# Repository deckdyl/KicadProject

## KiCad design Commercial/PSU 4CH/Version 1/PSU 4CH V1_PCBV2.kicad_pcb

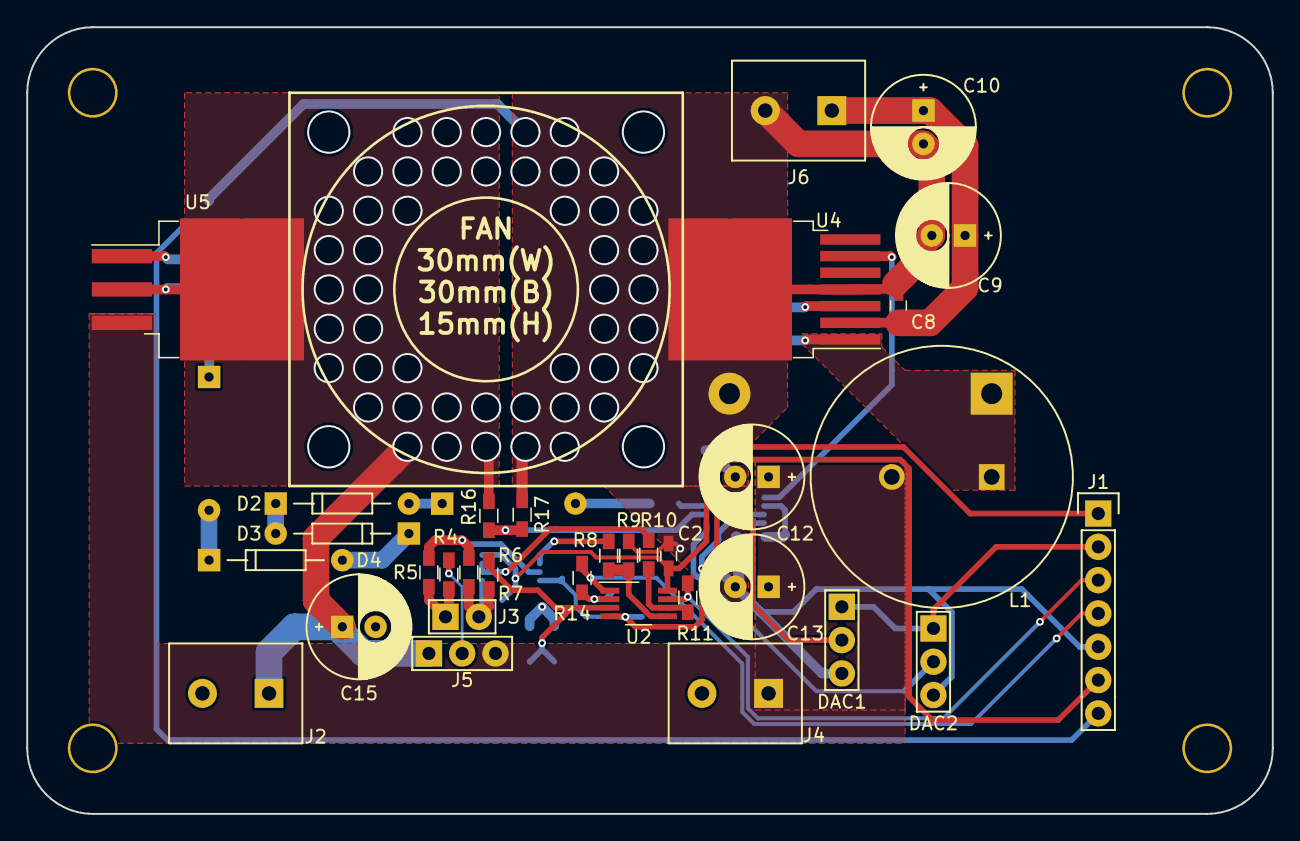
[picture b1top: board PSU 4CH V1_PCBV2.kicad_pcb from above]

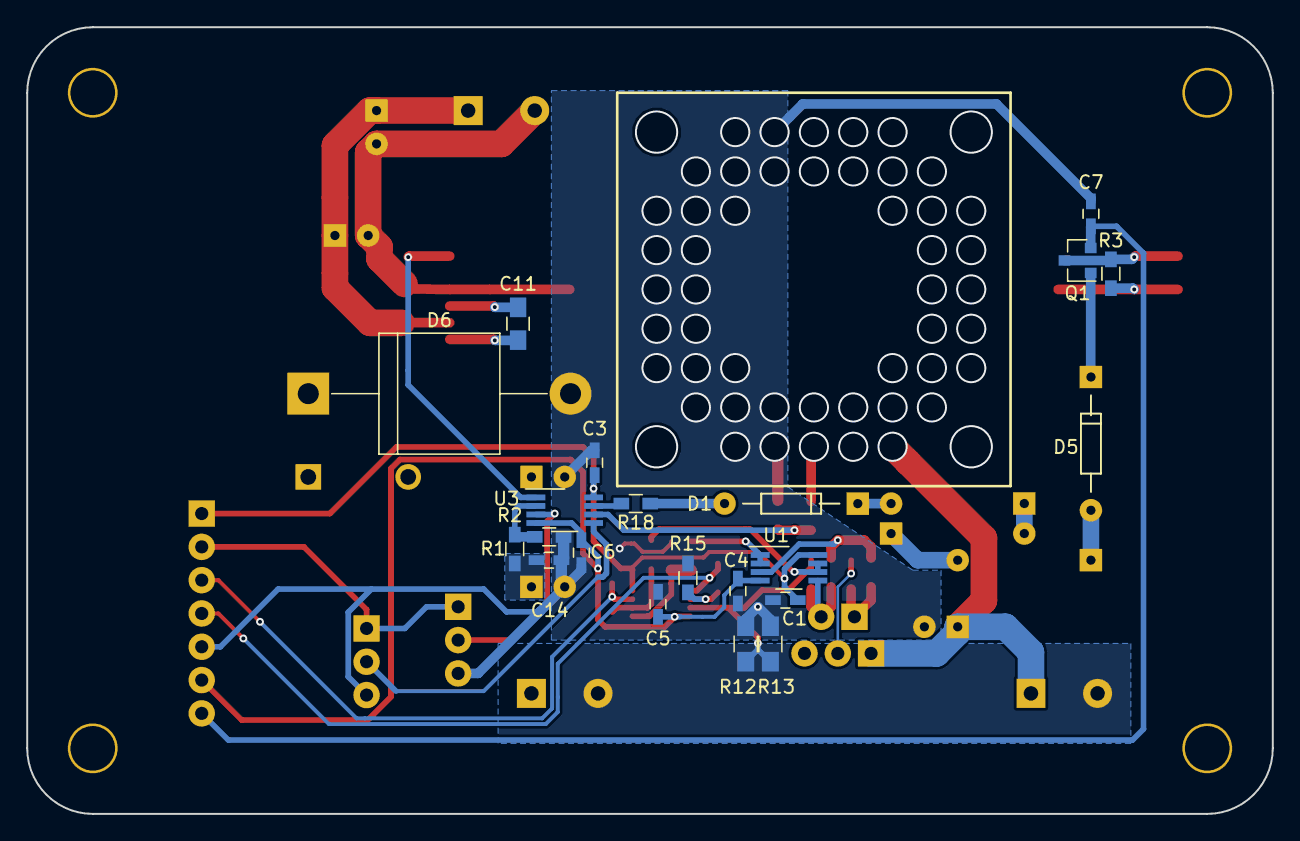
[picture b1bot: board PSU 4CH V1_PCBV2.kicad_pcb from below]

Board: 2 copper layers, 95.0 x 60.0 mm, 54 parts (21 on the bottom side), 35 nets.

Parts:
C1, C2, C3, C4, C5, C6, C7, C8, C14: 470nF; C_0603_HandSoldering
C9, C10, C12, C13, C15: 22uF; Cap_Pol_Radial_D8_P2
C11: 10nF; C_0805_HandSoldering
D1, D2, D3, D4, D5: 1N914; 1N4148
D6: 15SQ045; D_P600_R-6_P20.00mm_Horizontal
DAC1: BUCK_DAC; Pin_Header_Straight_1x03
DAC2: LINEAR DAC; Pin_Header_Straight_1x03
J1: MCU I/O; Pin_Header_Straight_1x07
J2, J4: PSU Out; Terminal_Block-5mm
J3: PSU FB; Pin_Header_Straight_1x02
J5: Select; Pin_Header_Straight_1x03
J6: Input; Terminal_Block-5mm
L1: 22uH; Inductor-22uH-5.4A
Q1: FJV1845; SOT-23
R1, R5, R16: 91kΩ; R_0603_HandSoldering
R2, R6, R17: 10kΩ; R_0603_HandSoldering
R3: 680Ω; R_0603_HandSoldering
R4, R7: 10Ω; R_0603_HandSoldering
R8, R9, R10, R11, R15: 1kΩ; R_0603_HandSoldering
R12, R13: 12mΩ; R_0805_HandSoldering
R14: 100kΩ; R_0603_HandSoldering
R18: 75kΩ; R_0603_HandSoldering
U1, U2, U3: LMP2022; VSSOP-8_3.0x3.0mm_Pitch0.65mm
U4: LM2678SX-ADJ; TO-263-7_TabPin4
U5: LMS1585A; TO-263-3_TabPin2

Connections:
+3V3: DAC1.1, DAC2.1, J1.2
+5V: C1.1, C2.1, C3.1, J1.1, U1.8, U2.8, U3.8
-0V5: C4.2, C5.2, C6.2, J1.6, U1.4, U2.4, U3.4
-2V8: C7.2, J1.7, Q1.2
/DAC_BUCK: DAC1.2, U3.3
/DAC_LINEAR: DAC2.2, U3.5
/I-ADC: J1.4, R14.1, U2.1
/Input-V+: C8.1, C9.1, C10.1, J6.1, U4.2
/Output-Buck: C12.1, C13.1, C14.1, J4.1, J5.3, L1.2, R1.1, U5.3
/Output-GND: J2.2, J4.2, R7.2, R12.1, R13.1, U2.3
/Output-Linear: C15.1, J2.1, J5.1, R3.1, R16.1, U5.2
/V-ADC: J1.3, R11.1, U2.7
/Vfb+: J3.1, R4.2, R5.1
/Vfb-: J3.2, R6.2, R7.1, U1.5
/Vfb-Buck: U3.1, U4.6
/Vfb-Linear: Q1.3, R3.2, U5.1
GND: C1.2, C2.2, C3.2, C4.1, C5.1, C6.1, C7.1, C8.2, C9.2, C10.2, C12.2, C13.2, C14.2, C15.2, D6.2, DAC1.3, DAC2.3, J1.5, J6.2, R2.2, R9.2, R12.2, R13.2, R15.2, R17.2, U4.4
unnamed: C11.1, D6.1, L1.1, U4.1
unnamed: C11.2, U4.3
unnamed: D1.1, D2.2
unnamed: D1.2, R18.1
unnamed: D2.1, D3.2
unnamed: D3.1, D4.2
unnamed: D4.1, D5.2
unnamed: D5.1, Q1.1
unnamed: J5.2, R4.1
unnamed: R1.2, R2.1, U3.2
unnamed: R5.2, R6.1, U1.3
unnamed: R8.1, R9.1, U2.5
unnamed: R8.2, U1.1, U1.2
unnamed: R10.1, R11.2, U2.6
unnamed: R10.2, U1.6, U1.7
unnamed: R14.2, R15.1, U2.2
unnamed: R16.2, R17.1, U3.6
unnamed: R18.2, U3.7

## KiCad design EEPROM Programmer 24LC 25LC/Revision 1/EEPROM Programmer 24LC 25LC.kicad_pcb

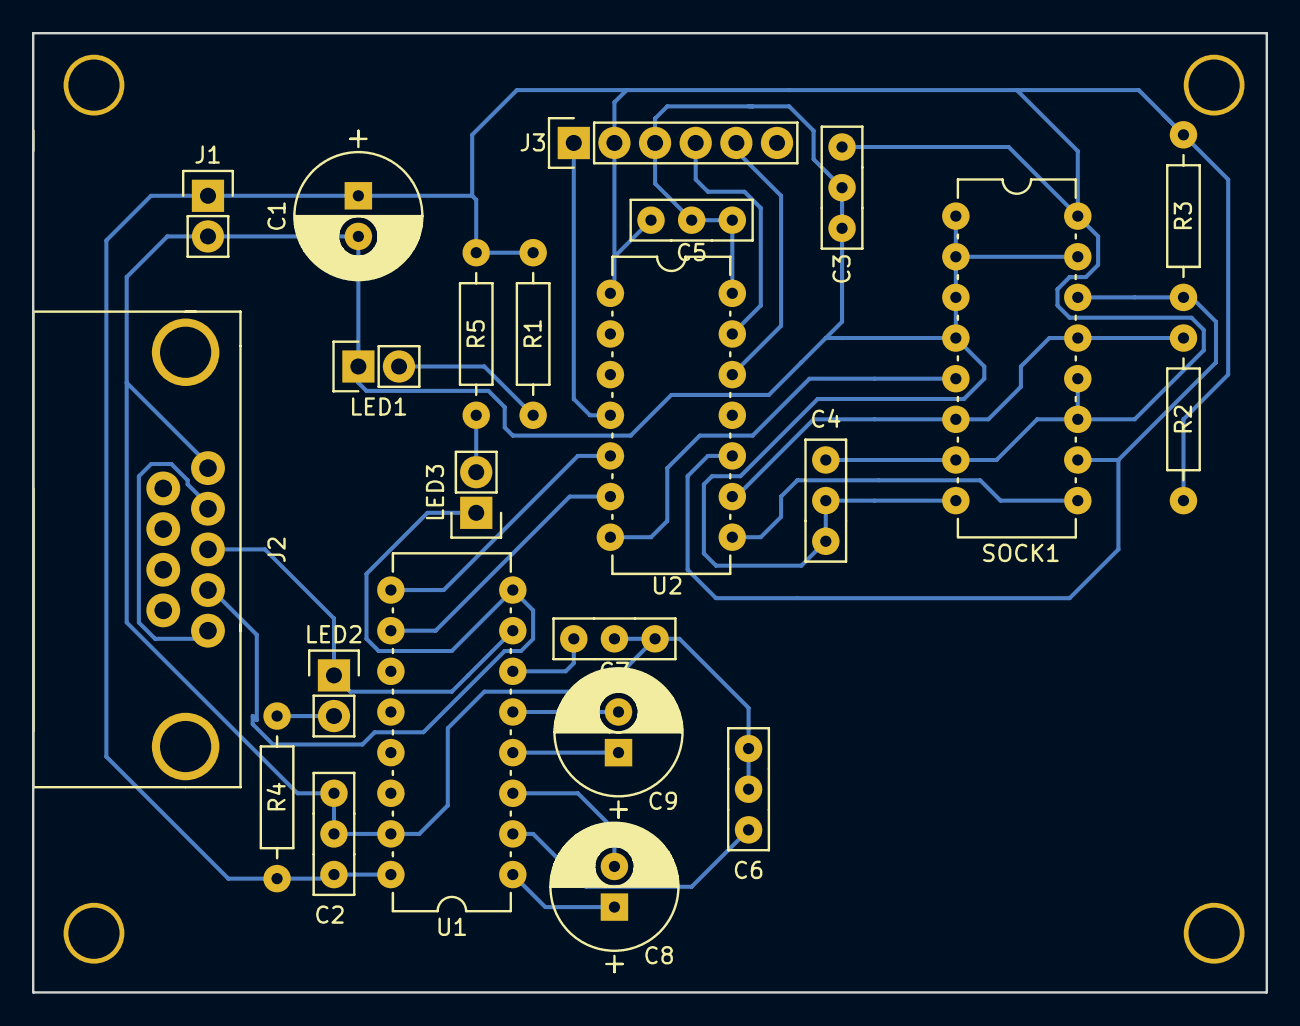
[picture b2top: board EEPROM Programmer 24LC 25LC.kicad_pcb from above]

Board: 2 copper layers, 77.1 x 59.9 mm, 23 parts (0 on the bottom side), 23 nets.

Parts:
C1: 100uF; Cap_Pol_Radial_D8_P2
C2, C3, C4, C5, C6, C7: 100nF; Cap_UnPol_P3
C8, C9: 1uF; Cap_Pol_Radial_D8_P2
J1: Power; Pin_Header_Straight_1x02
J2: RS232 DB9; RS232_DB9_Female_PCB_Mount
J3: PICKIT; Pin_Header_Straight_1x06
LED1: PWR_red; Pin_Header_Straight_1x02
LED2: RX_Yellow; Pin_Header_Straight_1x02
LED3: TX_Yellow; Pin_Header_Straight_1x02
R1: 390Ω; Resistor-0.25W
R2, R3: 4.7kΩ; Resistor-0.25W
R4, R5: 1kΩ; Resistor-0.25W
SOCK1: Test_Socket_16pin; IC_PDIP_16pin
U1: MAX232; IC_PDIP_16pin
U2: PIC16F1825; IC_PDIP_14pin

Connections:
+5V: C1.1, C2.1, C3.1, C4.1, C5.1, J1.1, J3.2, R1.2, R2.2, R3.2, R4.1, R5.1, SOCK1.7, SOCK1.11, SOCK1.12, SOCK1.16, U1.16, U2.1
CS: SOCK1.5, U2.7
GND: C1.2, C2.2, C3.2, C4.2, C5.2, C6.2, C7.2, J1.2, J2.5, J3.3, LED1.1, SOCK1.1, SOCK1.2, SOCK1.3, SOCK1.4, SOCK1.8, SOCK1.15, U1.15, U2.14
ICSPCLK: J3.5, U2.12
ICSPDAT: J3.4, U2.13
MCLR: J3.1, U2.4
M_SPI_In: R2.1, SOCK1.6, SOCK1.13, U2.9
M_SPI_Out: SOCK1.9, U2.8
unnamed: C6.1, U1.2
unnamed: C7.1, U1.6
unnamed: C8.1, U1.1
unnamed: C8.2, U1.3
unnamed: C9.1, U1.4
unnamed: C9.2, U1.5
unnamed: J2.1, J2.4
unnamed: J2.2, LED3.1, U1.8
unnamed: J2.3, LED2.1, U1.7
unnamed: LED1.2, R1.1
unnamed: LED2.2, R4.2
unnamed: LED3.2, R5.2
RX: U1.9, U2.5
SCK: R3.1, SOCK1.10, SOCK1.14, U2.10
TX: U1.10, U2.6

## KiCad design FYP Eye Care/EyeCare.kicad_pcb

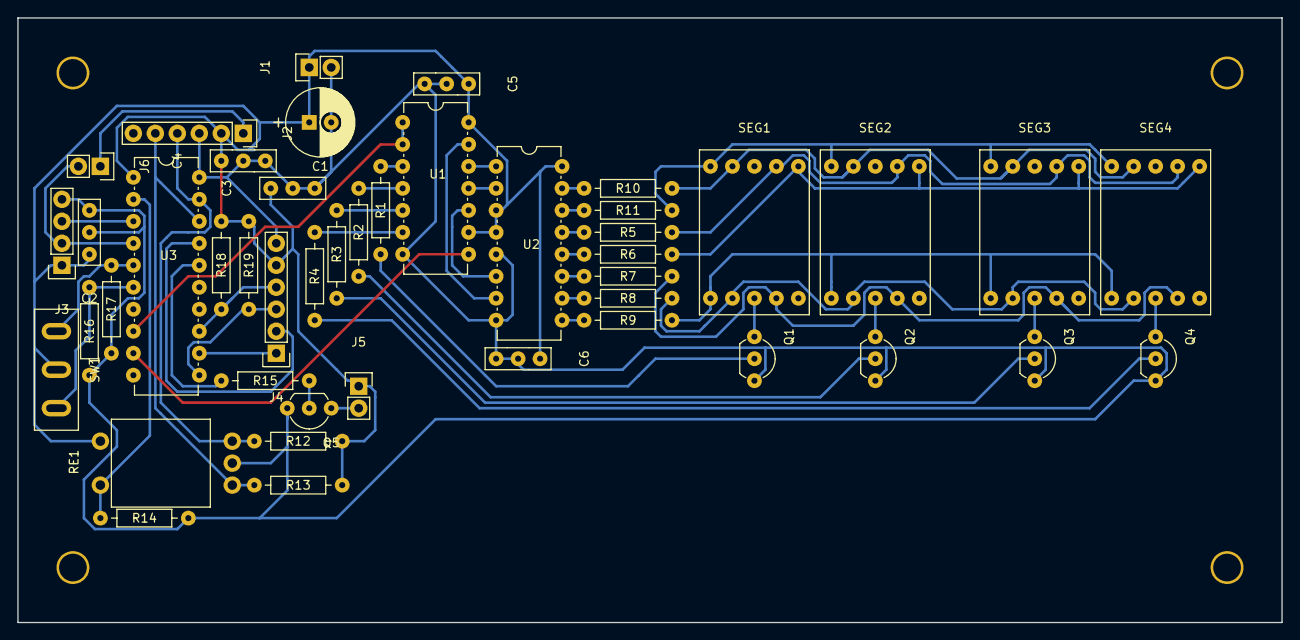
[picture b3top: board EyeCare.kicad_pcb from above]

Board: 2 copper layers, 146.1 x 69.9 mm, 45 parts (0 on the bottom side), 49 nets.

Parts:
C1: 100uF; Cap_Pol_Radial_D8_P2
C2, C3, C4, C5, C6: 100nF; Cap_UnPol_P3
J1: PWR; Pin_Header_Straight_1x02
J2: PICKIT; Pin_Header_Straight_1x06
J3: Sensor; Pin_Header_Straight_1x04
J4: DS3231; Pin_Header_Straight_1x06
J5: Buzzer; Pin_Header_Straight_1x02
J6: Jumper; Pin_Header_Straight_1x02
Q1, Q2, Q3, Q4, Q5: 2N3904; TO-92_Inline_Wide
R1, R2, R3, R4, R15: 470Ω; Resistor-0.25W
R5, R6, R7, R8, R9, R10, R11: 180Ω; Resistor-0.25W
R12, R13, R14, R16, R17: 10kΩ; Resistor-0.25W
R18, R19: 3.9kΩ; Resistor-0.25W
RE1: Rotary_Encoder
SEG1, SEG2, SEG3, SEG4: 7Segment_CC; 7Seg_small
SW1: Switch; Switch_3-Pin
U1: 74LS164; IC_PDIP_14pin
U2: 4511; IC_PDIP_16pin
U3: PIC16F1509; IC_PDIP_20pin

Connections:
32K: J4.1, U3.12
Buzzer: R15.1, U3.16
CLK: U1.8, U3.9
D0: Q4.2, R4.2
D1: Q3.2, R3.2
D2: Q2.2, R2.2
D3: Q1.2, R1.2
DI: U1.1, U1.2, U3.8
Echo: J3.3, U3.3
unnamed: J5.2, Q5.1
unnamed: Q1.1, SEG1.3,8
unnamed: Q2.1, SEG2.3,8
unnamed: Q3.1, SEG3.3,8
unnamed: Q4.1, SEG4.3,8
unnamed: Q5.2, R15.2
unnamed: R1.1, U1.3
unnamed: R2.1, U1.4
unnamed: R3.1, U1.5
unnamed: R4.1, U1.6
unnamed: R5.1, SEG1.7, SEG2.7, SEG3.7, SEG4.7
unnamed: R5.2, U2.13
unnamed: R6.1, SEG1.6, SEG2.6, SEG3.6, SEG4.6
unnamed: R6.2, U2.12
unnamed: R7.1, SEG1.4, SEG2.4, SEG3.4, SEG4.4
unnamed: R7.2, U2.11
unnamed: R8.1, SEG1.2, SEG2.2, SEG3.2, SEG4.2
unnamed: R8.2, U2.10
unnamed: R9.1, SEG1.1, SEG2.1, SEG3.1, SEG4.1
unnamed: R9.2, U2.9
unnamed: R10.1, SEG1.9, SEG2.9, SEG3.9, SEG4.9
unnamed: R10.2, U2.15
unnamed: R11.1, SEG1.10, SEG2.10, SEG3.10, SEG4.10
unnamed: R11.2, U2.14
unnamed: U1.10, U2.6
unnamed: U1.11, U2.2
unnamed: U1.12, U2.1
unnamed: U1.13, U2.7
PGC: J2.5, R13.2, RE1.5, U3.18
PGD: J2.4, R12.2, RE1.3, U3.19
RotarySW: R14.1, RE1.2, U3.2
SCL: J4.3, R19.2, U3.11
SDA: J4.4, R18.2, U3.13
SQW: J4.2, U3.17
SW1: R17.1, SW1.1, U3.5
SW2: R16.1, SW1.3, U3.6
Trigger: J3.2, J6.2, U3.4
Vdd: C1.1, C2.1, C3.1, C4.1, C5.1, C6.1, J1.1, J2.2, J3.1, J4.5, J5.1, R12.1, R13.1, R18.1, R19.1, RE1.1, SW1.2, U1.9, U1.14, U2.3, U2.4, U2.16, U3.1
Vpp: J2.1, J6.1
Vss: C1.2, C2.2, C3.2, C4.2, C5.2, C6.2, J1.2, J2.3, J3.4, J4.6, Q1.3, Q2.3, Q3.3, Q4.3, Q5.3, R14.2, R16.2, R17.2, RE1.4, U1.7, U2.5, U2.8, U3.20

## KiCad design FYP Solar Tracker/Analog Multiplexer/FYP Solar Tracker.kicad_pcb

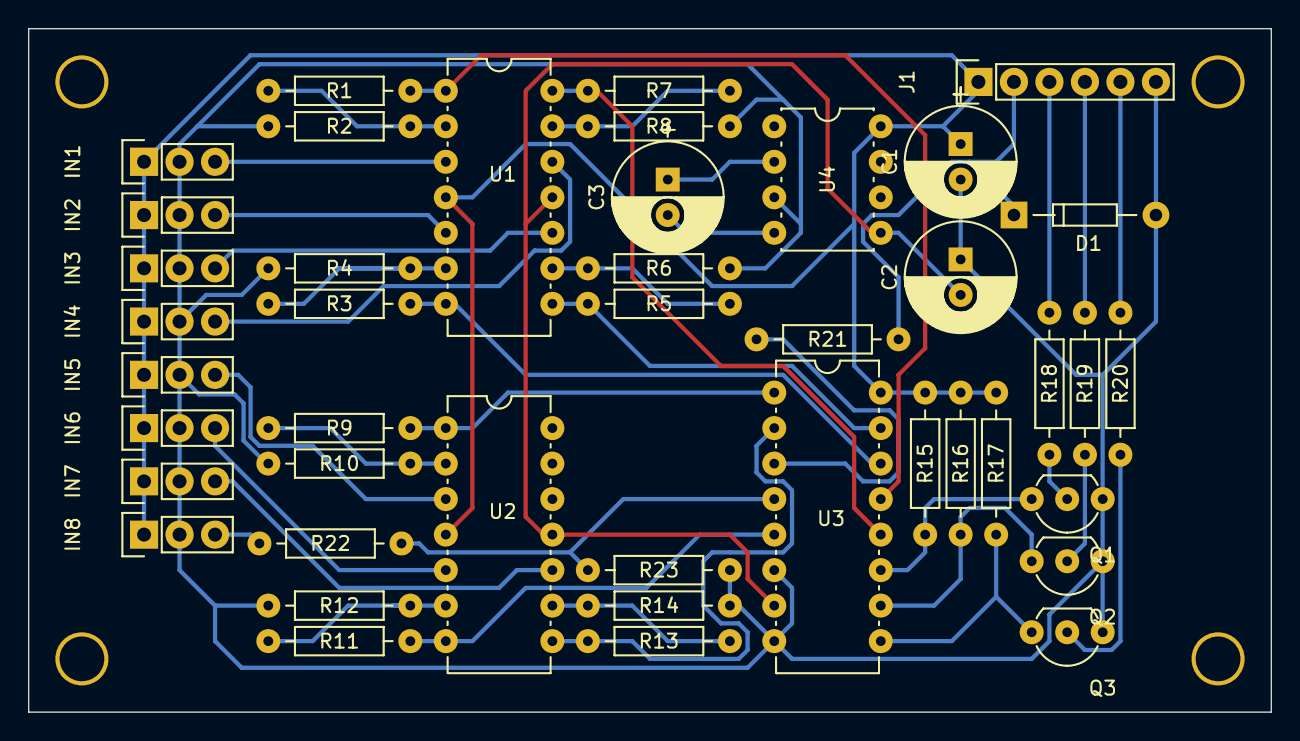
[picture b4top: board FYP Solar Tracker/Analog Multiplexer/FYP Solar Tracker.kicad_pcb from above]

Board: 2 copper layers, 88.9 x 48.9 mm, 43 parts (0 on the bottom side), 39 nets.

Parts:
C1, C2, C3: 10uF; Cap_Pol_Radial_D8_P2
D1: 4.7V; 1N4148
IN1, IN2, IN3, IN4, IN5, IN6, IN7, IN8: Header_1X3; Pin_Header_Straight_1x03
J1: MCU; Pin_Header_Straight_1x06
Q1, Q2, Q3: 2N3904; TO-92_Inline_Wide
R1, R3, R5, R9, R11, R13, R22: 27kΩ; Resistor-0.25W
R2, R4, R6, R7, R10, R12, R14, R15, R16, R17, R18, R19, R20, R23: 10kΩ; Resistor-0.25W
R8: 12kΩ; Resistor-0.25W
R21: 1.2kΩ; Resistor-0.25W
U1, U2: LM324; IC_PDIP_14pin
U3: 4051; IC_PDIP_16pin
U4: TC962; IC_PDIP_8pin

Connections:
+9V: C1.1, IN1.1, IN2.1, IN3.1, IN4.1, IN5.1, IN6.1, IN7.1, IN8.1, J1.1, R15.1, R16.1, R17.1, U1.4, U2.4, U3.16, U4.8
CH0: R1.1, U1.1, U3.13
CH1: R3.1, U1.7, U3.14
CH2: R5.1, U1.8, U3.15
CH3: R7.1, U1.14, U3.12
CH4: R9.1, U2.1, U3.1
CH5: R11.1, U2.7, U3.5
CH6: R13.1, U2.8, U3.2
CH7: R22.2, R23.1, U3.4
GND: C1.2, C2.1, D1.2, IN1.2, IN2.2, IN3.2, IN4.2, IN5.2, IN6.2, IN7.2, IN8.2, J1.6, Q1.1, Q2.1, Q3.1, R2.2, R4.2, R6.2, R8.2, R10.2, R12.2, R14.2, R23.2, U3.6, U3.8, U4.3
unnamed: C2.2, U1.11, U2.11, U3.7, U4.5
unnamed: C3.1, U4.2
unnamed: C3.2, U4.4
unnamed: D1.1, J1.2, R21.2
unnamed: IN1.3, U1.3
unnamed: IN2.3, U1.5
unnamed: IN3.3, U1.10
unnamed: IN4.3, U1.12
unnamed: IN5.3, U2.3
unnamed: IN6.3, U2.5
unnamed: IN7.3, U2.10
unnamed: IN8.3, R22.1
unnamed: J1.3, R18.1
unnamed: J1.4, R19.1
unnamed: J1.5, R20.1
unnamed: Q1.2, R18.2
unnamed: Q1.3, R15.2, U3.11
unnamed: Q2.2, R19.2
unnamed: Q2.3, R16.2, U3.10
unnamed: Q3.2, R20.2
unnamed: Q3.3, R17.2, U3.9
unnamed: R1.2, R2.1, U1.2
unnamed: R3.2, R4.1, U1.6
unnamed: R5.2, R6.1, U1.9
unnamed: R7.2, R8.1, U1.13
unnamed: R9.2, R10.1, U2.2
unnamed: R11.2, R12.1, U2.6
unnamed: R13.2, R14.1, U2.9
unnamed: R21.1, U3.3

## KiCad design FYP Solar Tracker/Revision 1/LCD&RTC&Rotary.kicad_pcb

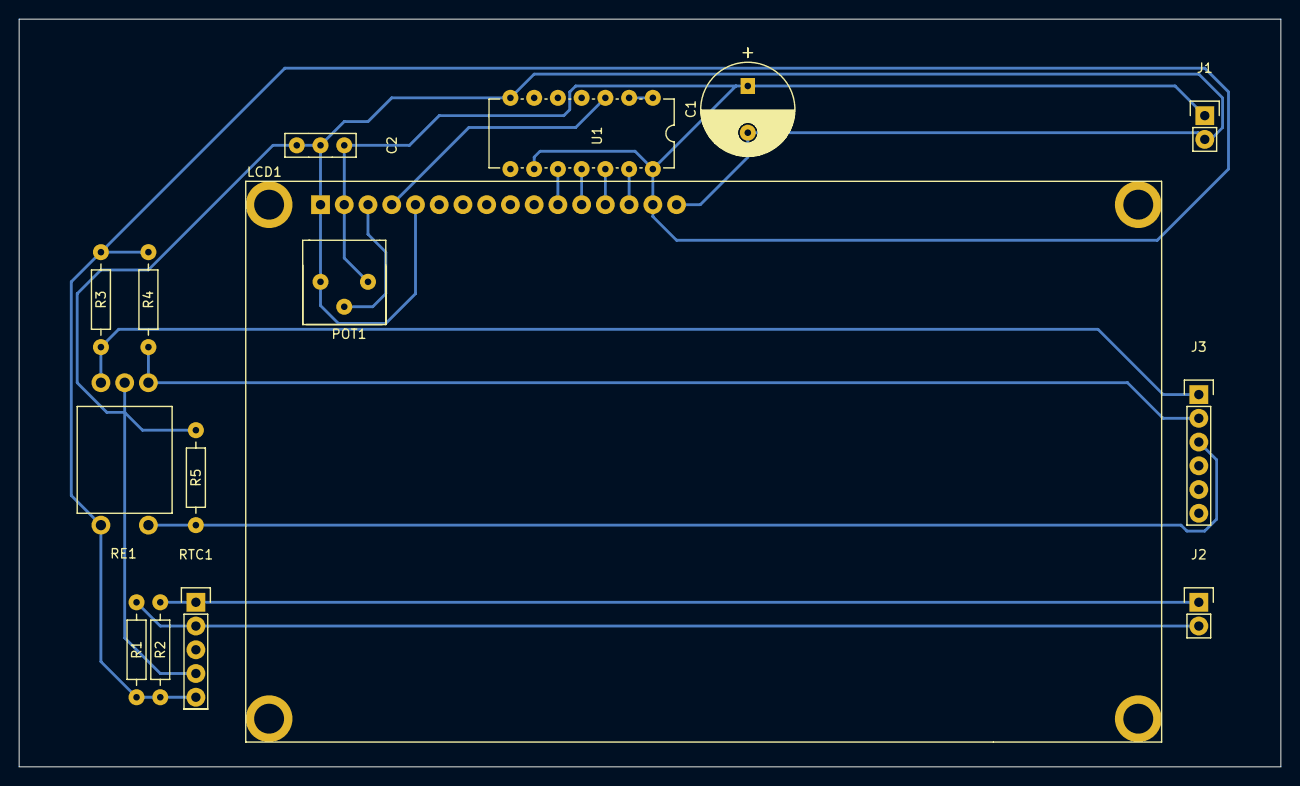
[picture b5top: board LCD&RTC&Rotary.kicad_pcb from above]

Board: 2 copper layers, 135.0 x 80.0 mm, 15 parts (0 on the bottom side), 16 nets.

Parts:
C1: 100uF; Cap_Pol_Radial_D10_P3
C2: 100nF; Cap_UnPol_P3
J1: PWR; Pin_Header_Straight_1x02
J2: I2C; Pin_Header_Straight_1x02
J3: I/O; Pin_Header_Straight_1x06
LCD1: LCD 2004; LCD_2004
POT1: 10kΩ; Potentiometer_Bourns_3386
R1, R2: 3.9kΩ; Resistor-0.25W
R3, R4, R5: 10kΩ; Resistor-0.25W
RE1: Rotary_Encoder
RTC1: DS1307; Pin_Header_Straight_1x05
U1: 74LS164; IC_PDIP_14pin

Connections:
+5V: C1.1, C2.1, J1.1, LCD1.2, LCD1.15, POT1.1, R1.1, R2.1, R3.1, R4.1, RE1.1, RTC1.5, U1.9, U1.14
GND: C1.2, C2.2, J1.2, LCD1.1, LCD1.5, LCD1.16, POT1.3, R5.2, RE1.4, RTC1.4, U1.7
LCD_CLK: J3.5, U1.8
LCD_DAT: J3.6, U1.1, U1.2
LCD_EN: J3.4, LCD1.6
unnamed: LCD1.3, POT1.2
unnamed: LCD1.4, U1.3
unnamed: LCD1.11, U1.10
unnamed: LCD1.12, U1.11
unnamed: LCD1.13, U1.12
unnamed: LCD1.14, U1.13
RE1: J3.1, R3.2, RE1.3
RE2: J3.2, R4.2, RE1.5
SCL: J2.2, R1.2, RTC1.2
SDA: J2.1, R2.2, RTC1.1
SW: J3.3, R5.1, RE1.2

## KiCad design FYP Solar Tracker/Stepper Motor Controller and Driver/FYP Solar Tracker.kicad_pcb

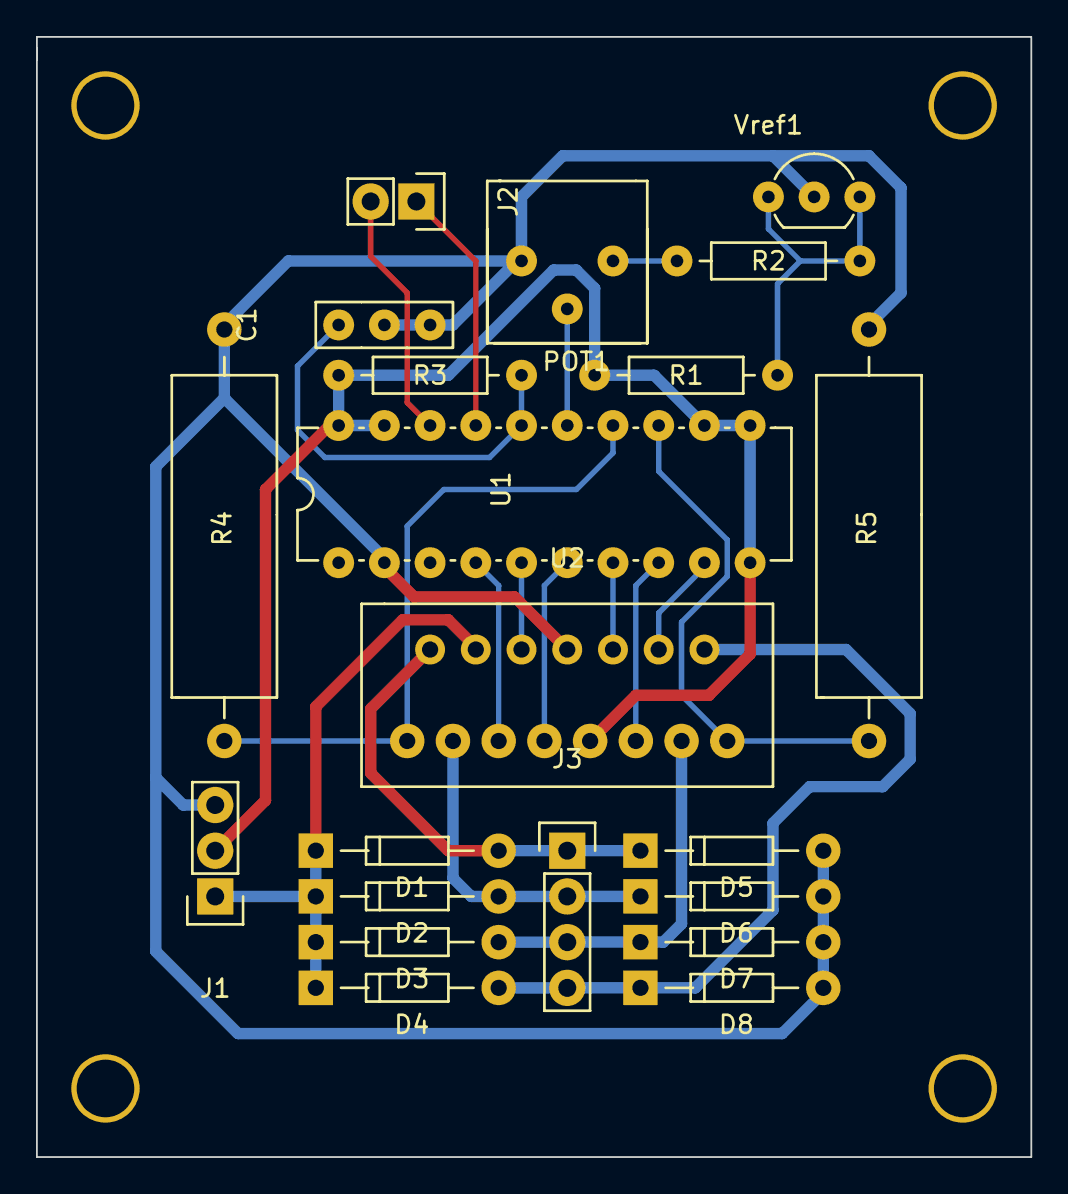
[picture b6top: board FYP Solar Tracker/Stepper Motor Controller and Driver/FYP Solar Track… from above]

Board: 2 copper layers, 55.2 x 62.2 mm, 21 parts (0 on the bottom side), 21 nets.

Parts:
C1: 10nF; Cap_UnPol_P3
D1, D2, D3, D4, D5, D6, D7, D8: 1N5818; 1N4148
J1: POWER; Pin_Header_Straight_1x03
J2: I/O; Pin_Header_Straight_1x02
J3: Motor; Pin_Header_Straight_1x04
POT1: 1kΩ; Potentiometer_Bourns_3386
R1: 1.2kΩ; Resistor-0.25W
R2: 1.5kΩ; Resistor-0.25W
R3: 10kΩ; Resistor-0.25W
R4, R5: 1Ω; Resistor-2W
U1: L297; IC_PDIP_20pin
U2: L298
Vref1: TL431; TO-92_Inline_Wide

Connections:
0.5Vref: POT1.2, U1.15
+5V: J1.2, R1.1, R3.1, U1.10, U1.11, U1.12, U1.19, U1.20, U2.9
GND: C1.2, D5.2, D6.2, D7.2, D8.2, J1.3, POT1.3, R4.2, R5.2, U1.2, U2.8, Vref1.2
MotorClk: J2.2, U1.18
MotorDir: J2.1, U1.17
unnamed: C1.1, R3.2, U1.16
unnamed: D1.1, D2.1, D3.1, D4.1, J1.1, U2.4
unnamed: D1.2, D5.1, J3.1, U2.2
unnamed: D2.2, D6.1, J3.2, U2.3
unnamed: D3.2, D7.1, J3.3, U2.13
unnamed: D4.2, D8.1, J3.4, U2.14
unnamed: POT1.1, R2.2
unnamed: R1.2, R2.1, Vref1.1, Vref1.3
unnamed: U1.4, U2.5
unnamed: U1.5, U2.6
unnamed: U1.6, U2.7
unnamed: U1.7, U2.10
unnamed: U1.8, U2.11
unnamed: U1.9, U2.12
Sense1: R4.1, U1.14, U2.1
Sense2: R5.1, U1.13, U2.15

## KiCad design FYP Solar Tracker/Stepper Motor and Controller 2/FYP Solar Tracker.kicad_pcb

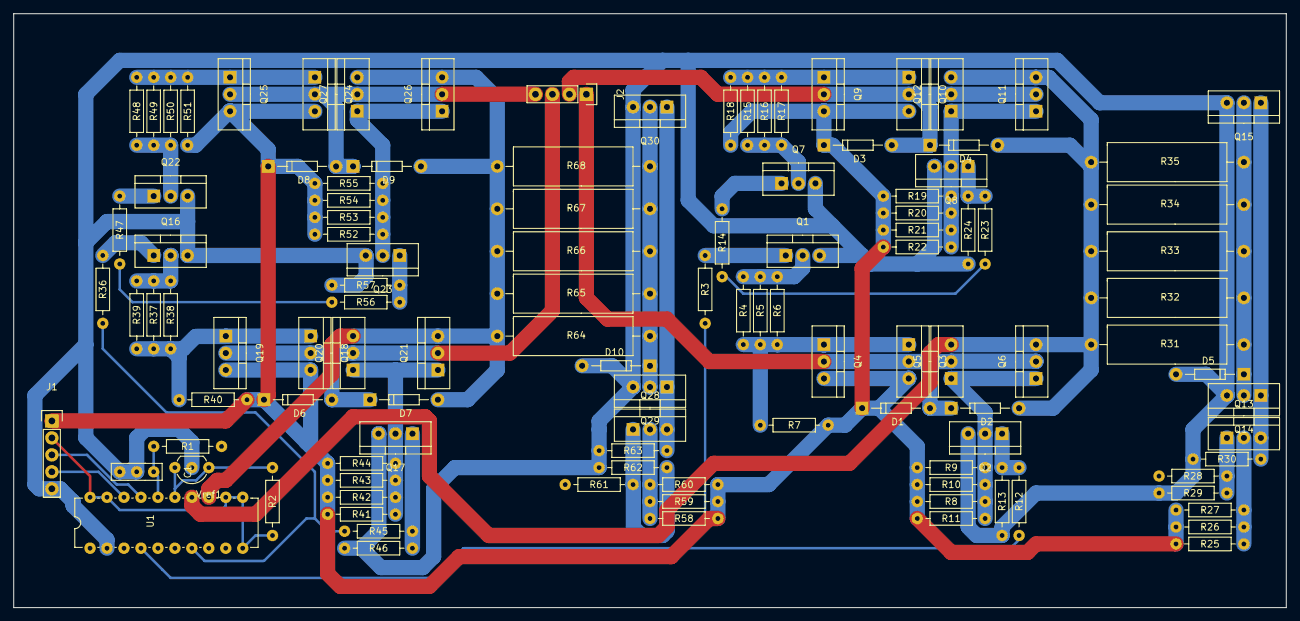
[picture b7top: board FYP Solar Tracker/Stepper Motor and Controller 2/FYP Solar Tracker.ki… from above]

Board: 2 copper layers, 190.5 x 88.9 mm, 113 parts (0 on the bottom side), 47 nets.

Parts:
C1: 10nF; Cap_UnPol_P3
D1, D2, D3, D4, D5, D6, D7, D8, D9, D10: SR204
J1: PWR_IO; Pin_Header_Straight_1x05
J2: Motor; Pin_Header_Straight_1x04
Q1, Q2, Q5, Q6, Q7, Q8, Q11, Q12, Q13, Q14, Q15, Q16, Q17, Q20, Q21, Q22, Q23, Q26, Q27, Q28, Q29, Q30: TIP41; TO-220_Neutral123_Vertical
Q3, Q4, Q9, Q10, Q18, Q19, Q24, Q25: TIP42; TO-220_Neutral123_Vertical
R1: 10kΩ; Resistor-0.25W
R2, R12, R23, R28, R45, R56, R61: 1.2kΩ; Resistor-0.25W
R3, R14, R36, R47: 820Ω; Resistor-0.25W
R4, R5, R6, R15, R16, R17, R37, R38, R39, R48, R49, R50: 56Ω; Resistor-0.25W
R7, R13, R18, R24, R29, R30, R40, R46, R51, R57, R62, R63: 0Ω; Resistor-0.25W
R8, R9, R19, R20, R41, R42, R52, R53: 220Ω; Resistor-0.25W
R10, R11, R21, R22, R43, R44, R54, R55: 270Ω; Resistor-0.25W
R25, R26, R27, R58, R59, R60: 100Ω; Resistor-0.25W
R31, R32, R34, R35, R64, R65, R67, R68: 3.3Ω; Resistor-2W
R33, R66: 1.5Ω; Resistor-2W
U1: L297; IC_PDIP_20pin
Vref1: TL431; TO-92_Inline_Wide

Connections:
+5V: J1.2, R2.1, U1.10, U1.11, U1.12, U1.19, U1.20
+12V: D1.1, D3.1, D6.1, D8.1, J1.1, Q3.3, Q4.3, Q9.3, Q10.3, Q18.3, Q19.3, Q24.3, Q25.3, R7.1, R8.1, R9.1, R10.1, R11.1, R18.1, R19.1, R20.1, R21.1, R22.1, R25.1, R26.1, R27.1, R40.1, R41.1, R42.1, R43.1, R44.1, R51.1, R52.1, R53.1, R54.1, R55.1, R58.1, R59.1, R60.1
A: R3.2, R12.2, U1.4
B: R14.2, R23.2, U1.6
C: R36.2, R45.2, U1.7
D: R47.2, R56.2, U1.9
GND: C1.2, D5.2, D10.2, J1.5, Q1.3, Q2.3, Q7.3, Q8.3, Q14.3, Q15.3, Q16.3, Q17.3, Q22.3, Q23.3, Q29.3, Q30.3, R13.2, R24.2, R29.2, R30.2, R46.2, R57.2, R62.2, R63.2, U1.2, Vref1.2
INA: D1.2, D2.1, J2.1, Q3.2, Q4.2, Q5.2, Q6.2
INB: D3.2, D4.1, J2.2, Q9.2, Q10.2, Q11.2, Q12.2
INC: D6.2, D7.1, J2.3, Q18.2, Q19.2, Q20.2, Q21.2
IND: D8.2, D9.1, J2.4, Q24.2, Q25.2, Q26.2, Q27.2
INH1: R28.2, U1.5
INH2: R61.2, U1.8
MotorClk: J1.4, U1.18
MotorDir: J1.3, U1.17
unnamed: C1.1, R1.2, U1.16
unnamed: D5.1, Q14.2, Q15.2, R31.2, R32.2, R33.2, R34.2, R35.2
unnamed: D10.1, Q29.2, Q30.2, R64.2, R65.2, R66.2, R67.2, R68.2
unnamed: Q1.1, R3.1
unnamed: Q1.2, R4.2, R5.2, R6.2
unnamed: Q2.1, R12.1, R13.1
unnamed: Q2.2, Q5.1, Q6.1, R8.2, R9.2, R10.2, R11.2
unnamed: Q3.1, Q4.1, R4.1, R5.1, R6.1, R7.2
unnamed: Q7.1, R14.1
unnamed: Q7.2, R15.2, R16.2, R17.2
unnamed: Q8.1, R23.1, R24.1
unnamed: Q9.1, Q10.1, R15.1, R16.1, R17.1, R18.2
unnamed: Q8.2, Q11.1, Q12.1, R19.2, R20.2, R21.2, R22.2
unnamed: Q13.1, R28.1, R29.1
unnamed: Q13.2, R25.2, R26.2, R27.2
unnamed: Q13.3, Q14.1, Q15.1, R30.1
unnamed: Q16.1, R36.1
unnamed: Q16.2, R37.2, R38.2, R39.2
unnamed: Q17.1, R45.1, R46.1
unnamed: Q17.2, Q20.1, Q21.1, R41.2, R42.2, R43.2, R44.2
unnamed: Q18.1, Q19.1, R37.1, R38.1, R39.1, R40.2
unnamed: Q22.1, R47.1
unnamed: Q22.2, R48.2, R49.2, R50.2
unnamed: Q23.1, R56.1, R57.1
unnamed: Q23.2, Q26.1, Q27.1, R52.2, R53.2, R54.2, R55.2
unnamed: Q24.1, Q25.1, R48.1, R49.1, R50.1, R51.2
unnamed: Q28.1, R61.1, R62.1
unnamed: Q28.2, R58.2, R59.2, R60.2
unnamed: Q28.3, Q29.1, Q30.1, R63.1
Vref: R2.2, U1.15, Vref1.1, Vref1.3
sense1: D2.2, D4.2, Q5.3, Q6.3, Q11.3, Q12.3, R31.1, R32.1, R33.1, R34.1, R35.1, U1.14
sense2: D7.2, D9.2, Q20.3, Q21.3, Q26.3, Q27.3, R64.1, R65.1, R66.1, R67.1, R68.1, U1.13

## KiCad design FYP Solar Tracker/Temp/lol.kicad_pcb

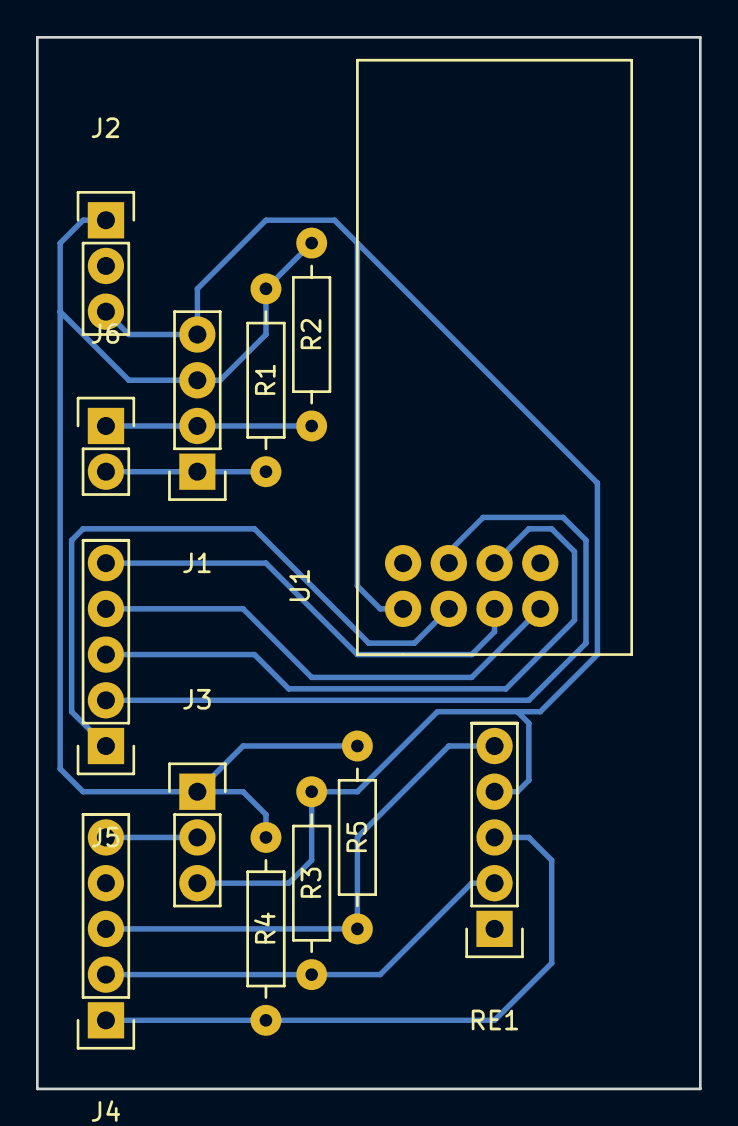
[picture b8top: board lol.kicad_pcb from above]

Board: 2 copper layers, 36.8 x 58.4 mm, 13 parts (0 on the bottom side), 14 nets.

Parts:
J1: LCD; Pin_Header_Straight_1x04
J2: PWR; Pin_Header_Straight_1x03
J3: IR; Pin_Header_Straight_1x03
J4, J5: Header_1X5; Pin_Header_Straight_1x05
J6: Header_1X2; Pin_Header_Straight_1x02
R1, R2: 3.9kΩ; Resistor-0.25W
R3, R4, R5: 10k; Resistor-0.25W
RE1: Rotary_Encoder; Pin_Header_Straight_1x05
U1: NRF24L01

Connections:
+3V3: J2.2, U1.2
+5V: J1.3, J2.1, J3.1, R1.2, R2.2, R4.1, R5.1, RE1.1
D2: J4.1, R4.2, RE1.3
D3: J4.2, R3.1, RE1.2
D4: J4.3, R5.2, RE1.5
D6: J3.2, J4.5
D9: J5.1, U1.3
D10: J5.2, U1.4
D11: J5.3, U1.6
D12: J5.4, U1.7
D13: J5.5, U1.5
GND: J1.4, J2.3, J3.3, R3.2, RE1.4, U1.1
SCL: J1.1, J6.2, R1.1
SDA: J1.2, J6.1, R2.1
